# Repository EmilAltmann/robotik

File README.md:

# robotik

Um die Biblithek nutzen zu können muss sie zu erst importiert werden. Dazu geht man unter "Sketch > Include Library > Add .ZIP Library" und wählt die Robotik.zip Datei aus.

Jedes Programm benötigt den Inport der Biblithek mit einem include.
```C
#include "Robotik.h"
```
In der setup Methode kann alles, was einmalig ausgefürt werden soll hinzugefügt werden. Jedoch muss dort immer die InitalisiereRobotik Methode zu beginn stehen.
```C
void setup() {
  InitialisiereRobotik();
}
```
Die loop Methode wird genutzt um Programmcode wiederholt auszufüren.
```C
void loop() {
}

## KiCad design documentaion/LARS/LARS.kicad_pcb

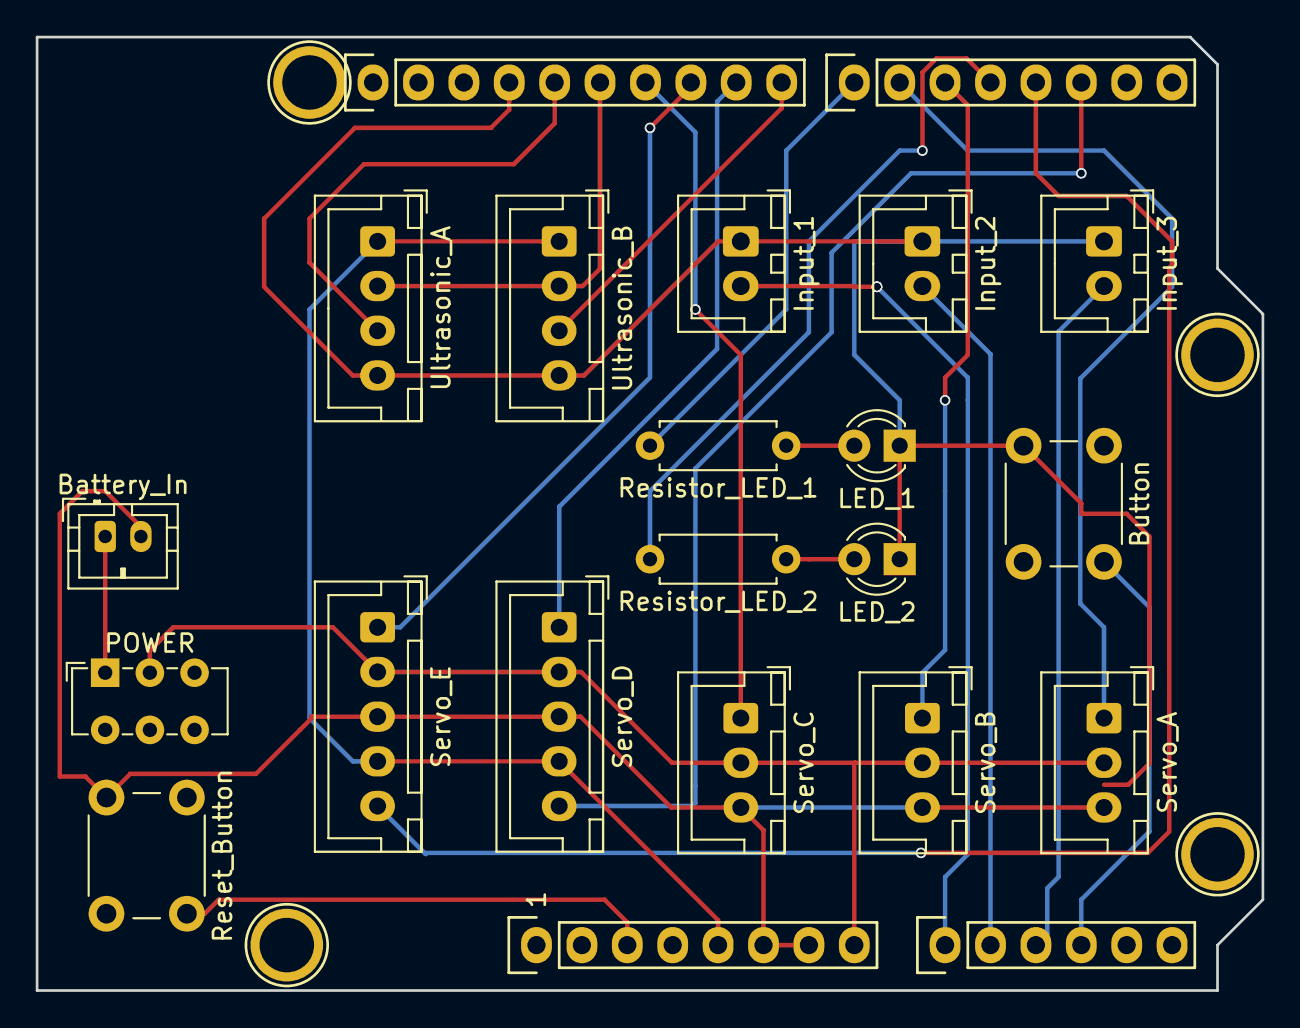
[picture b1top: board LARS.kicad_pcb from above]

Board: 2 copper layers, 68.6 x 53.3 mm, 26 parts (0 on the bottom side), 23 nets.

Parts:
Battery_In: Conn_01x02; JST_PH_B2B-PH-K_1x02_P2.00mm_Vertical
Button: SW_Push; SW_PUSH_6mm_H4.3mm
Input_1, Input_2, Input_3: Conn_01x02; JST_XH_B2B-XH-A_1x02_P2.50mm_Vertical
LED_1, LED_2: red; LED_D3.0mm
P1: Power; Socket_Strip_Arduino_1x08
P2: Analog; Socket_Strip_Arduino_1x06
P3: Digital; Socket_Strip_Arduino_1x10
P4: Digital; Socket_Strip_Arduino_1x08
P5, P6, P7, P8: CONN_01X01; Arduino_1pin
POWER: SW_DPST_x2; SW_E-Switch_EG1271_DPDT
Reset_Button: SW_Push; SW_PUSH_6mm_H4.3mm
Resistor_LED_1, Resistor_LED_2: 610; R_Axial_DIN0207_L6.3mm_D2.5mm_P7.62mm_Horizontal
Servo_A: Conn_01x03; JST_XH_B3B-XH-A_1x03_P2.50mm_Vertical
Servo_B: Conn_01x03; JST_XH_B3B-XH-A_1x03_P2.50mm_Vertical
Servo_C: Conn_01x03; JST_XH_B3B-XH-A_1x03_P2.50mm_Vertical
Servo_D: Conn_01x05; JST_XH_B5B-XH-A_1x05_P2.50mm_Vertical
Servo_E: Conn_01x05; JST_XH_B5B-XH-A_1x05_P2.50mm_Vertical
Ultrasonic_A: Conn_01x04; JST_XH_B4B-XH-A_1x04_P2.50mm_Vertical
Ultrasonic_B: Conn_01x04; JST_XH_B4B-XH-A_1x04_P2.50mm_Vertical

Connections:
2: P4.6, Servo_D.5
3(**): P4.5, Servo_E.5
4: P4.4, Resistor_LED_2.2
5(**): P4.3, Servo_B.1
6(**): P4.2, Servo_A.1
7: P4.1, Resistor_LED_1.2
8: P3.10, Ultrasonic_B.3
9(**): P3.9, Servo_D.1
10(**): P3.8, Servo_E.1
11(**): P3.7, Servo_C.1
12: P3.6, Ultrasonic_A.2, Ultrasonic_B.2
13: P3.5, Ultrasonic_A.3
+5V: P1.5, Servo_D.4, Servo_E.4, Ultrasonic_A.1, Ultrasonic_B.1
A0: Input_1.2, P2.1
A1: Input_2.2, P2.2
A2: Input_3.2, P2.3
A3: Button.1, P2.4
GND: Battery_In.2, Button.2, Input_1.1, Input_2.1, Input_3.1, LED_1.1, LED_2.1, P1.6, P1.7, P3.4, Reset_Button.2, Servo_A.3, Servo_B.3, Servo_C.3, Servo_D.3, Servo_E.3, Ultrasonic_A.4, Ultrasonic_B.4
unnamed: Battery_In.1, POWER.1
unnamed: LED_1.2, Resistor_LED_1.1
unnamed: LED_2.2, Resistor_LED_2.1
Reset: P1.3, Reset_Button.1
Vin: P1.8, POWER.2, Servo_A.2, Servo_B.2, Servo_C.2, Servo_D.2, Servo_E.2

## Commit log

2023-09-11 Bugfix!
    fixes integer division to double precision devition
2023-09-13 Create test
2023-09-15 copied files
2023-09-15 Revert "copied files"
    This reverts commit 9d99663a13eeb9aa85572d51817cdaa2c9cf0c01.
2023-09-15 moved files
2023-09-15 work has to be done
2023-09-15 added simple schematic
2023-09-19 refracted and expanded documentation
2023-09-19 renamed picures to pictures
2023-09-19 renamed .JPG to .jpg
2023-09-28 Added info about the KiCAD PCB design
